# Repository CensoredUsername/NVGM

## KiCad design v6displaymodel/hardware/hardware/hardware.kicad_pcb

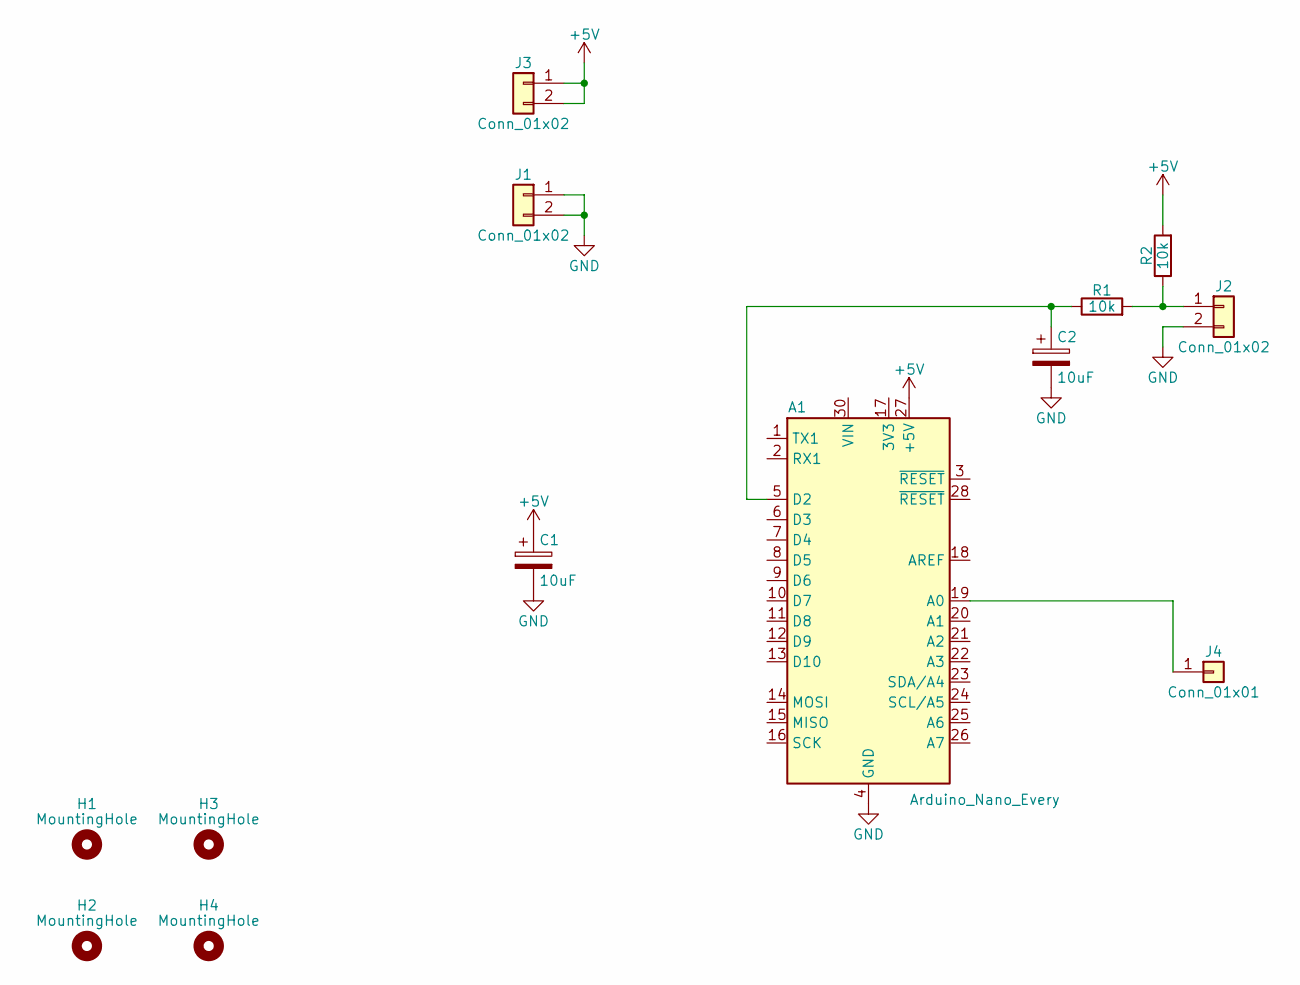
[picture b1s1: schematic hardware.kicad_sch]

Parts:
A1: Arduino_Nano_Every; Arduino_Nano
C1, C2: 10uF; CP_Radial_D5.0mm_P2.50mm
H1, H2, H3, H4: MountingHole; MountingHole_3.2mm_M3
J1, J2, J3: Conn_01x02; PinHeader_1x02_P2.54mm_Vertical
J4: Conn_01x01; PinHeader_1x01_P2.54mm_Vertical
R1, R2: 10k; R_Axial_DIN0204_L3.6mm_D1.6mm_P5.08mm_Horizontal

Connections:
+5V: A1.27 (+5V), C1.1, J3.1, J3.2, R2.2
GND: A1.4 (GND), A1.29 (GND), C1.2, C2.2, J1.1, J1.2, J2.2
unnamed: A1.5 (D2), C2.1, R1.1
unnamed: J2.1, R1.2, R2.1
unnamed: A1.19 (A0), J4.1

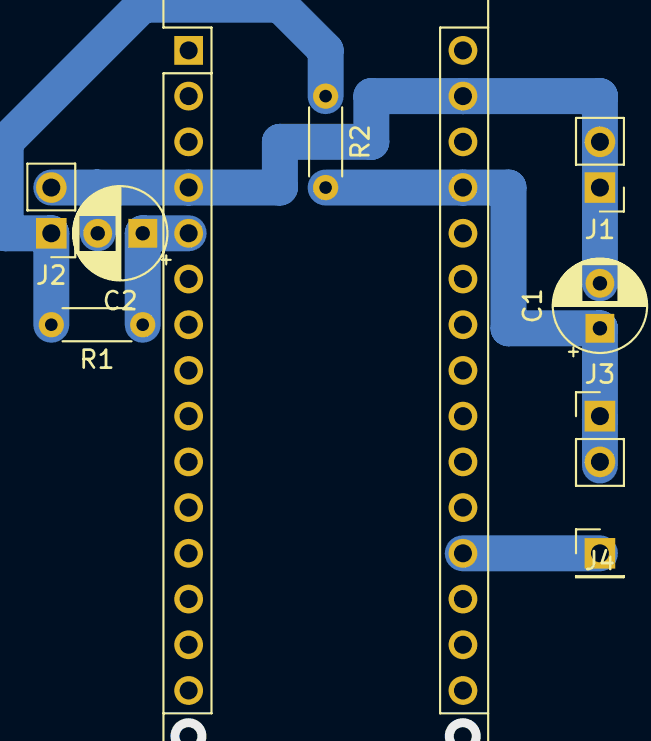
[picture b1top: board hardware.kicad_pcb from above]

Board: 2 copper layers, 13 parts (0 on the bottom side), 5 nets.

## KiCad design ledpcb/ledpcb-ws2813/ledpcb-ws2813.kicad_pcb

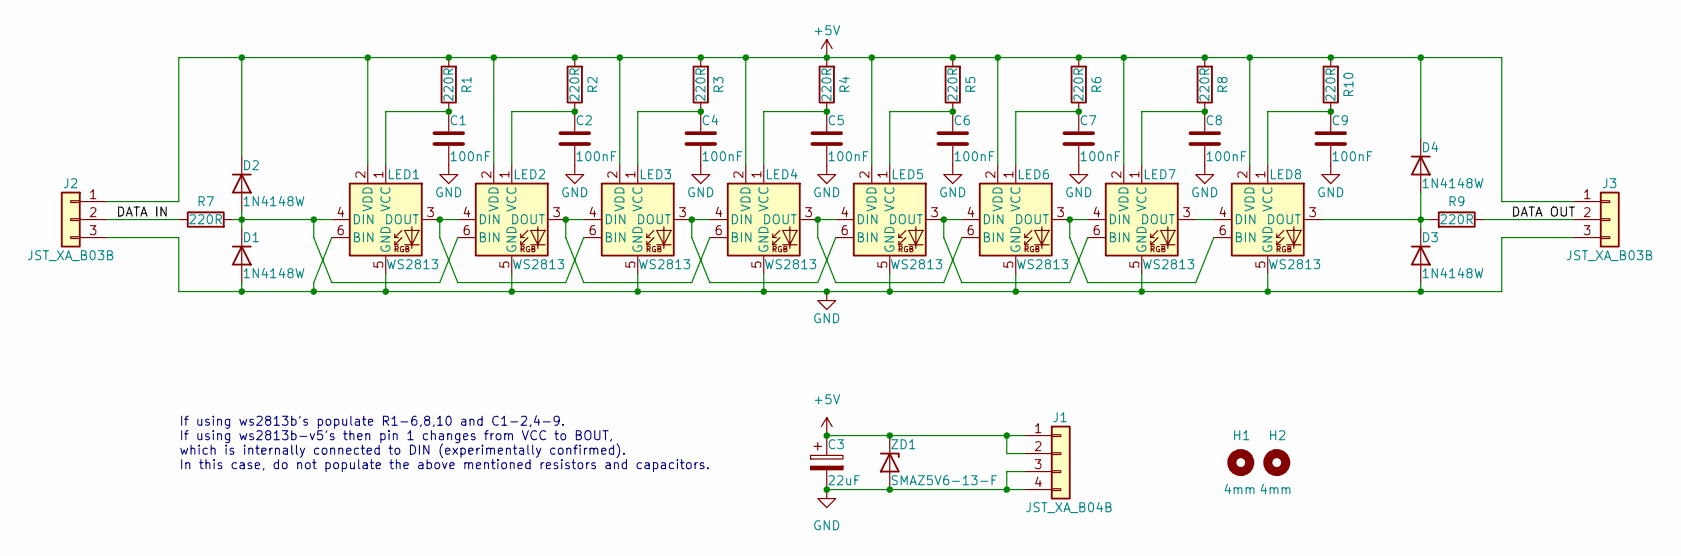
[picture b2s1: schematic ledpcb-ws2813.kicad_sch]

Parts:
C1, C2, C4, C5, C6, C7, C8, C9: 100nF; C_0603_1608Metric; LCSC C14663
C3: 22uF; C_Elec_6.3x5.4; LCSC C72505
D1, D2, D3, D4: 1N4148W; D_SOD-123; LCSC C81598
H1, H2: 4mm; MountingHole_3.2mm_M3
J1: JST_XA_B04B; JST_XA_B04B-XASK-1-A_1x04_P2.50mm_Vertical; LCSC C264994
J2, J3: JST_XA_B03B; JST_XA_B03B-XASK-1-A_1x03_P2.50mm_Vertical; LCSC C264992
LED1, LED2, LED3, LED4, LED5, LED6, LED7, LED8: WS2813; LED_WS2813_PLCC6_5.0x5.0mm_P1.6mm; LCSC C114592
R1, R2, R3, R4, R5, R6, R7, R8, R9, R10: 220R; R_0603_1608Metric; LCSC C22962
ZD1: SMAZ5V6-13-F; D_SMA; LCSC C5128847

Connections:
+5V: C3.1, D2.1 (K), D4.1 (K), J1.1, J1.2, J2.1, J3.1, LED1.2 (VDD), LED2.2 (VDD), LED3.2 (VDD), LED4.2 (VDD), LED5.2 (VDD), LED6.2 (VDD), LED7.2 (VDD), LED8.2 (VDD), R1.2, R2.2, R3.2, R4.2, R5.2, R6.2, R8.2, R10.2, ZD1.1 (K)
/DATA IN: J2.2, R7.1
/DATA OUT: J3.2, R9.1
GND: C1.2, C2.2, C3.2, C4.2, C5.2, C6.2, C7.2, C8.2, C9.2, D1.2 (A), D3.2 (A), J1.3, J1.4, J2.3, J3.3, LED1.5 (GND), LED1.6 (BIN), LED2.5 (GND), LED3.5 (GND), LED4.5 (GND), LED5.5 (GND), LED6.5 (GND), LED7.5 (GND), LED8.5 (GND), ZD1.2 (A)
unnamed: C1.1, LED1.1 (VCC), R1.1
unnamed: C2.1, LED2.1 (VCC), R2.1
unnamed: C4.1, LED3.1 (VCC), R3.1
unnamed: C5.1, LED4.1 (VCC), R4.1
unnamed: C6.1, LED5.1 (VCC), R5.1
unnamed: C7.1, LED6.1 (VCC), R6.1
unnamed: C8.1, LED7.1 (VCC), R8.1
unnamed: C9.1, LED8.1 (VCC), R10.1
unnamed: D1.1 (K), D2.2 (A), LED1.4 (DIN), LED2.6 (BIN), R7.2
unnamed: D3.1 (K), D4.2 (A), LED8.3 (DOUT), R9.2
unnamed: LED1.3 (DOUT), LED2.4 (DIN), LED3.6 (BIN)
unnamed: LED2.3 (DOUT), LED3.4 (DIN), LED4.6 (BIN)
unnamed: LED3.3 (DOUT), LED4.4 (DIN), LED5.6 (BIN)
unnamed: LED4.3 (DOUT), LED5.4 (DIN), LED6.6 (BIN)
unnamed: LED5.3 (DOUT), LED6.4 (DIN), LED7.6 (BIN)
unnamed: LED6.3 (DOUT), LED7.4 (DIN), LED8.6 (BIN)
unnamed: LED7.3 (DOUT), LED8.4 (DIN)

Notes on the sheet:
If using ws2813b's populate R1-6,8,10 and C1-2,4-9. If using ws2813b-v5's then pin 1 changes from VCC to BOUT, which is internally connected to DIN (experimentally confirmed). In this case, do not populate the above mentioned resistors and capacitors.

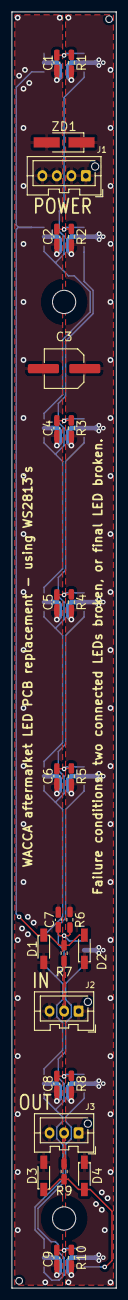
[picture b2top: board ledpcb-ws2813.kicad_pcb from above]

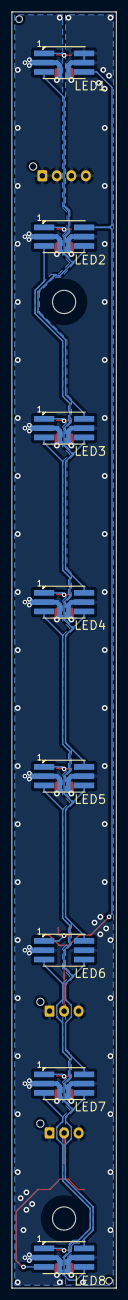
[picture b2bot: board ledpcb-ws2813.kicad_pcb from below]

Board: 2 copper layers, 18.0 x 220.0 mm, 37 parts (8 on the bottom side), 21 nets.

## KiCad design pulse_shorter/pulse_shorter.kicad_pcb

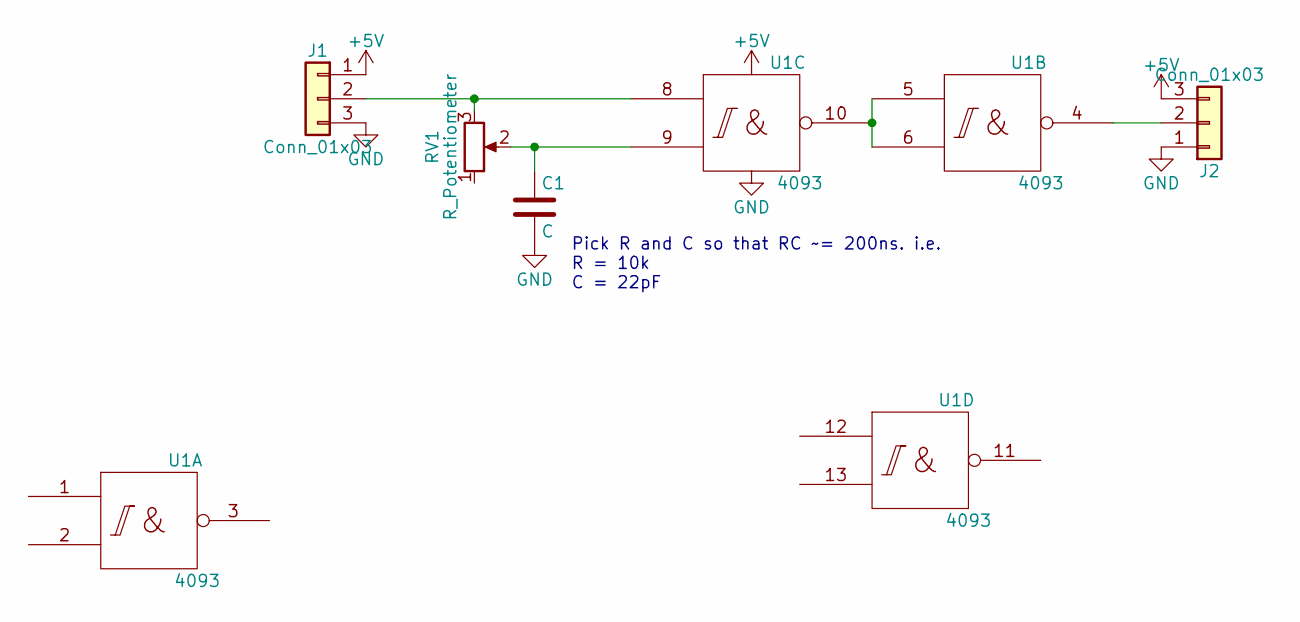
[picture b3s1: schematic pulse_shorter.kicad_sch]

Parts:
C1: C; C_Disc_D3.0mm_W1.6mm_P2.50mm
J1, J2: Conn_01x03; PinHeader_1x03_P2.54mm_Vertical
RV1: R_Potentiometer; Potentiometer_Piher_PT-6-V_Vertical
U1: 4093; DIP-14_W7.62mm

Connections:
+5V: J1.1, J2.3, U1.14 (Vdd)
GND: C1.2, J1.3, J2.1, U1.7 (Vss)
unnamed: C1.1, RV1.2, U1.9
unnamed: J1.2, RV1.3, U1.8
unnamed: J2.2, U1.4
unnamed: U1.5, U1.6, U1.10

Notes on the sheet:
Pick R and C so that RC ~= 200ns. i.e. R = 10k C = 22pF

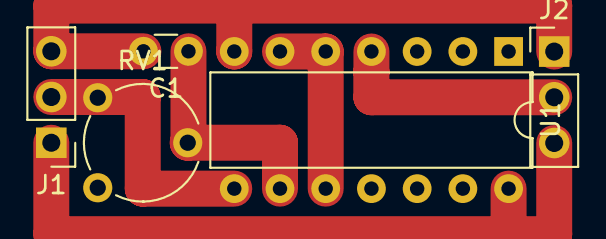
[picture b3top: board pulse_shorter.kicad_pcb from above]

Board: 2 copper layers, 5 parts (0 on the bottom side), 6 nets.

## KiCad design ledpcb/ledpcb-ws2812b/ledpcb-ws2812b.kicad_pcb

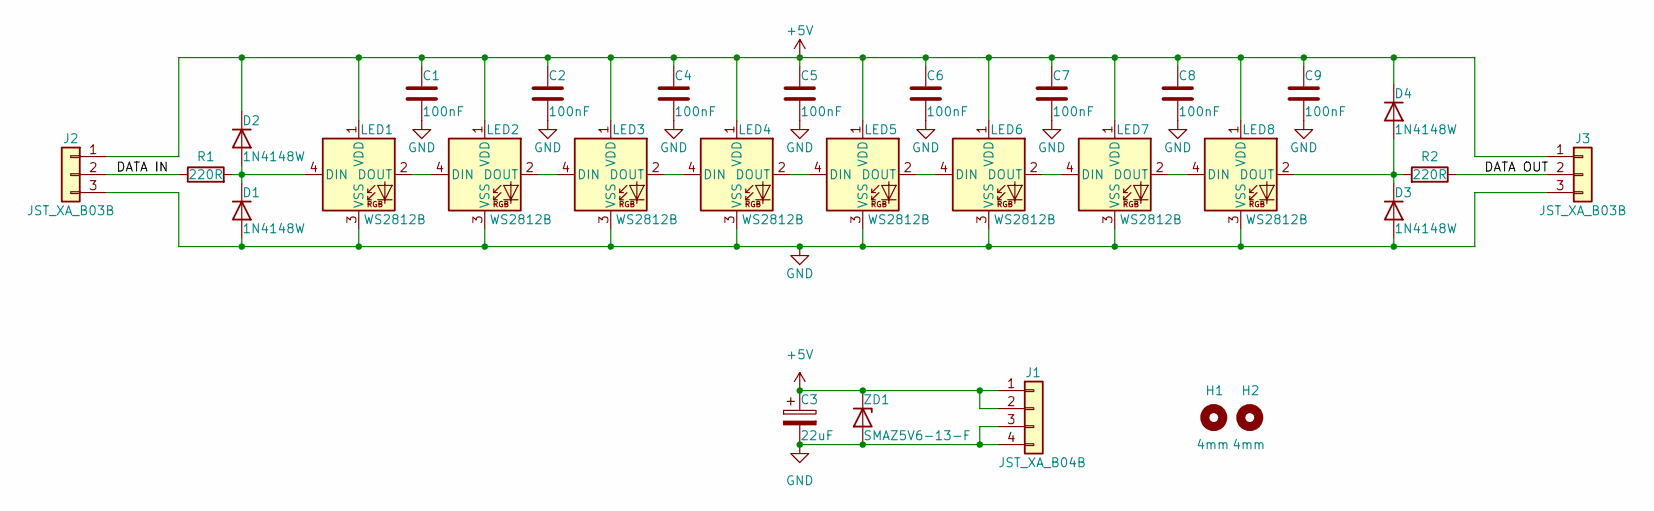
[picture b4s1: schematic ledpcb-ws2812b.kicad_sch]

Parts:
C1, C2, C4, C5, C6, C7, C8, C9: 100nF; C_0603_1608Metric; LCSC C14663
C3: 22uF; C_Elec_6.3x5.4; LCSC C72505
D1, D2, D3, D4: 1N4148W; D_SOD-123; LCSC C81598
H1, H2: 4mm; MountingHole_3.2mm_M3
J1: JST_XA_B04B; JST_XA_B04B-XASK-1-A_1x04_P2.50mm_Vertical; LCSC C264994
J2, J3: JST_XA_B03B; JST_XA_B03B-XASK-1-A_1x03_P2.50mm_Vertical; LCSC C264992
LED1, LED2, LED3, LED4, LED5, LED6, LED7, LED8: WS2812B; LED_WS2812B_PLCC4_5.0x5.0mm_P3.2mm; LCSC C2761795
R1, R2: 220R; R_0603_1608Metric; LCSC C22962
ZD1: SMAZ5V6-13-F; D_SMA; LCSC C110526

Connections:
+5V: C1.1, C2.1, C3.1, C4.1, C5.1, C6.1, C7.1, C8.1, C9.1, D2.1 (K), D4.1 (K), J1.1, J1.2, J2.1, J3.1, LED1.1 (VDD), LED2.1 (VDD), LED3.1 (VDD), LED4.1 (VDD), LED5.1 (VDD), LED6.1 (VDD), LED7.1 (VDD), LED8.1 (VDD), ZD1.1 (K)
/DATA IN: J2.2, R1.1
/DATA OUT: J3.2, R2.1
GND: C1.2, C2.2, C3.2, C4.2, C5.2, C6.2, C7.2, C8.2, C9.2, D1.2 (A), D3.2 (A), J1.3, J1.4, J2.3, J3.3, LED1.3 (VSS), LED2.3 (VSS), LED3.3 (VSS), LED4.3 (VSS), LED5.3 (VSS), LED6.3 (VSS), LED7.3 (VSS), LED8.3 (VSS), ZD1.2 (A)
unnamed: D1.1 (K), D2.2 (A), LED1.4 (DIN), R1.2
unnamed: D3.1 (K), D4.2 (A), LED8.2 (DOUT), R2.2
unnamed: LED1.2 (DOUT), LED2.4 (DIN)
unnamed: LED2.2 (DOUT), LED3.4 (DIN)
unnamed: LED3.2 (DOUT), LED4.4 (DIN)
unnamed: LED4.2 (DOUT), LED5.4 (DIN)
unnamed: LED5.2 (DOUT), LED6.4 (DIN)
unnamed: LED6.2 (DOUT), LED7.4 (DIN)
unnamed: LED7.2 (DOUT), LED8.4 (DIN)

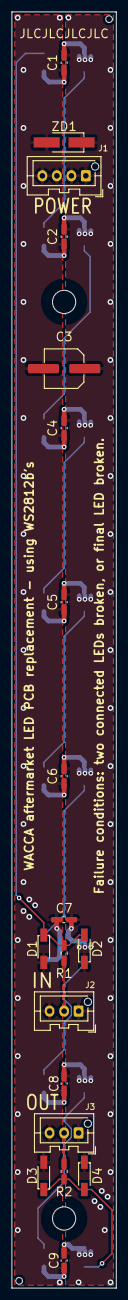
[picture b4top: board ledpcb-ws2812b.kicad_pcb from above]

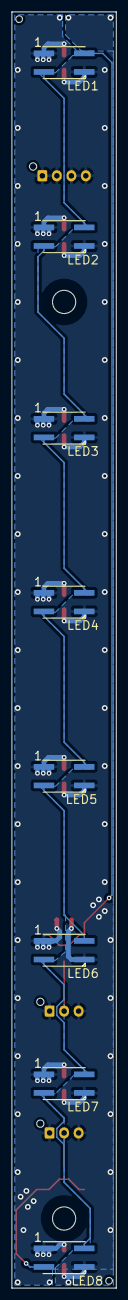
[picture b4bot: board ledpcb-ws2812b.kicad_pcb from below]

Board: 2 copper layers, 18.0 x 220.0 mm, 29 parts (8 on the bottom side), 13 nets.

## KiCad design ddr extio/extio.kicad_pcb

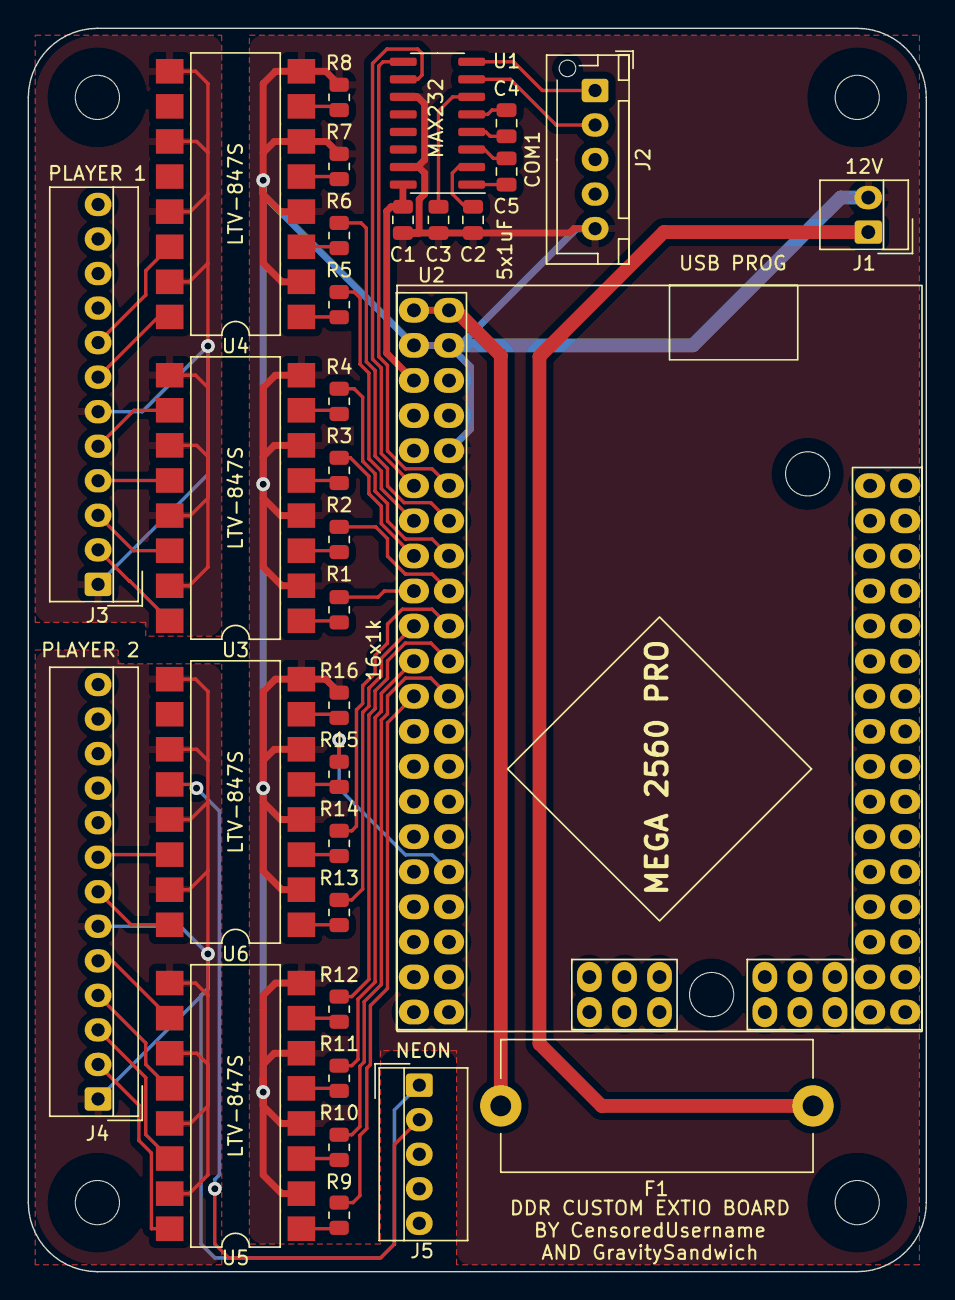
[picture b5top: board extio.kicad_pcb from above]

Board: 2 copper layers, 65.0 x 90.0 mm, 37 parts (0 on the bottom side), 58 nets.

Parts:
C1, C2, C3, C4, C5: 1uF; C_0805_2012Metric
F1: ?A; Fuseholder_Cylinder-5x20mm_Stelvio-Kontek_PTF78_Horizontal_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
H1, H2, H3, H4: M3; MountingHole_3.2mm_M3
J1: JST_NH_B02; JST_NH_B2P-SHF-1AA_1x02_P2.50mm_Vertical
J2: JST_XH_B05; JST_XH_B5B-XH-AM_1x05_P2.50mm_Vertical
J3: JST_NH_B12; JST_NH_B12P-SHF-1AA_1x12_P2.50mm_Vertical
J4: JST_NH_B13; JST_NH_B13P-SHF-1AA_1x13_P2.50mm_Vertical
J5: JST_NH_B05; JST_NH_B5P-SHF-1AA_1x05_P2.50mm_Vertical
R1, R2, R3, R4, R5, R6, R7, R8, R9, R10, R11, R12, R13, R14, R15, R16: 1k; R_0805_2012Metric
U1: MAX232; SOIC-16_3.9x9.9mm_P1.27mm
U2: Arduino_mega_2560_pro
U3, U4, U5, U6: LTV-847S; SMDIP-16_W9.53mm

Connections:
+5V: C1.1, U1.16 (VCC), U2.6 (5V)
+12V: F1.1, U2.1 (VIN), U2.2 (VIN)
/isolation1/Input A: R1.2, U2.18 (D7)
/isolation1/Input B: R2.2, U2.17 (D6)
/isolation1/Input C: R3.2, U2.16 (D5)
/isolation1/Input D: R4.2, U2.15 (D4)
/isolation1/Output A: J3.2, U3.16
/isolation1/Output B: J3.3, U3.14
/isolation1/Output C: J3.4, U3.12
/isolation1/Output D: J3.5, U3.10
/isolation2/Input A: R13.2, U2.20 (D9)
/isolation2/Input B: R14.2, U2.19 (D8)
/isolation2/Input C: R15.2, U2.33 (D22)
/isolation2/Output A: J4.7, U6.16
/isolation2/Output B: J4.8, U6.14
/isolation2/Output C: J5.2, U6.12
/isolation2/Output GND: J4.1, J4.6, J5.1, U5.9, U5.11, U5.13, U5.15, U6.9, U6.11, U6.13, U6.15
/isolation3/Input A: R9.2, U2.24 (D13)
/isolation3/Input B: R10.2, U2.23 (D12)
/isolation3/Input C: R11.2, U2.22 (D11)
/isolation3/Input D: R12.2, U2.21 (D10)
/isolation3/Output A: J4.2, U5.16
/isolation3/Output B: J4.3, U5.14
/isolation3/Output C: J4.4, U5.12
/isolation3/Output D: J4.5, U5.10
/isolation/Input A: R5.2, U2.14 (D3)
/isolation/Input B: R6.2, U2.13 (D2)
/isolation/Output A: J3.7, U4.16
/isolation/Output B: J3.8, U4.14
/isolation/Output GND: J3.1, J3.6, U3.9, U3.11, U3.13, U3.15, U4.9, U4.11, U4.13, U4.15
GND: C1.2, C2.2, C3.2, J1.2, J2.5, R7.2, R8.2, R16.2, U1.11 (T1IN), U1.15 (GND), U2.3 (GND), U2.4 (GND), U2.9 (AREF), U3.2, U3.4, U3.6, U3.8, U4.2, U4.4, U4.6, U4.8, U5.2, U5.4, U5.6, U5.8, U6.2, U6.4, U6.6, U6.8
unnamed: C2.1, U1.2 (VS+)
unnamed: C3.1, U1.6 (VS-)
unnamed: C4.1, U1.4 (C2+)
unnamed: C4.2, U1.5 (C2-)
unnamed: C5.1, U1.1 (C1+)
unnamed: C5.2, U1.3 (C1-)
unnamed: F1.2, J1.1
unnamed: J2.1, U1.8 (R2IN)
unnamed: J2.2, U1.7 (T2OUT)
unnamed: R1.1, U3.1
unnamed: R2.1, U3.3
unnamed: R3.1, U3.5
unnamed: R4.1, U3.7
unnamed: R5.1, U4.1
unnamed: R6.1, U4.3
unnamed: R7.1, U4.5
unnamed: R8.1, U4.7
unnamed: R9.1, U5.1
unnamed: R10.1, U5.3
unnamed: R11.1, U5.5
unnamed: R12.1, U5.7
unnamed: R13.1, U6.1
unnamed: R14.1, U6.3
unnamed: R15.1, U6.5
unnamed: R16.1, U6.7
unnamed: U1.9 (R2OUT), U2.11 (RX)
unnamed: U1.10 (T2IN), U2.12 (TX)

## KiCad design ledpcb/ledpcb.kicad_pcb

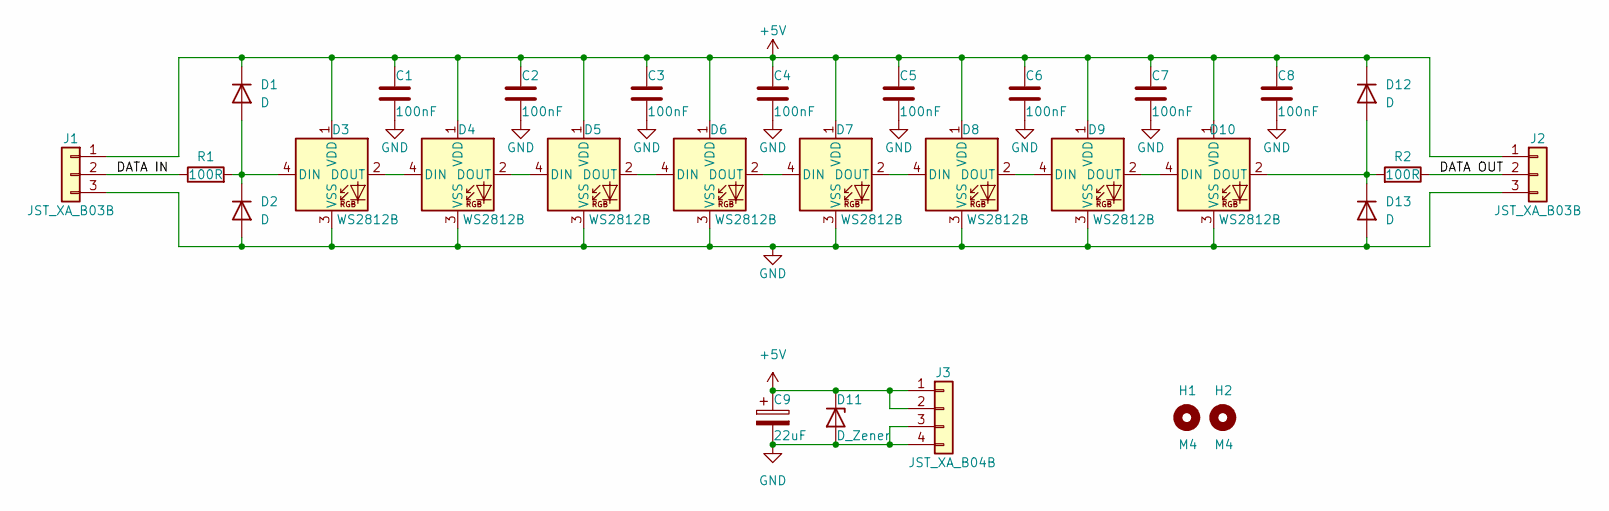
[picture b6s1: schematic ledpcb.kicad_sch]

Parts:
C1, C2, C3, C4, C5, C6, C7, C8: 100nF; C_0603_1608Metric
C9: 22uF; C_Elec_6.3x5.4
D1, D2, D12, D13: D; D_SOD-123
D3, D4, D5, D6, D7, D8, D9, D10: WS2812B; LED_WS2812B_PLCC4_5.0x5.0mm_P3.2mm
D11: D_Zener; D_SMA
H1, H2: M4; MountingHole_4.3mm_M4
J1, J2: JST_XA_B03B; JST_XA_B03B-XASK-1-A_1x03_P2.50mm_Vertical
J3: JST_XA_B04B; JST_XA_B04B-XASK-1-A_1x04_P2.50mm_Vertical
R1, R2: 100R; R_0603_1608Metric

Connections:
+5V: C1.1, C2.1, C3.1, C4.1, C5.1, C6.1, C7.1, C8.1, C9.1, D1.1 (K), D3.1 (VDD), D4.1 (VDD), D5.1 (VDD), D6.1 (VDD), D7.1 (VDD), D8.1 (VDD), D9.1 (VDD), D10.1 (VDD), D11.1 (K), D12.1 (K), J1.1, J2.1, J3.1, J3.2
/DATA IN: J1.2, R1.1
/DATA OUT: J2.2, R2.1
GND: C1.2, C2.2, C3.2, C4.2, C5.2, C6.2, C7.2, C8.2, C9.2, D2.2 (A), D3.3 (VSS), D4.3 (VSS), D5.3 (VSS), D6.3 (VSS), D7.3 (VSS), D8.3 (VSS), D9.3 (VSS), D10.3 (VSS), D11.2 (A), D13.2 (A), J1.3, J2.3, J3.3, J3.4
unnamed: D3.2 (DOUT), D4.4 (DIN)
unnamed: D1.2 (A), D2.1 (K), D3.4 (DIN), R1.2
unnamed: D4.2 (DOUT), D5.4 (DIN)
unnamed: D5.2 (DOUT), D6.4 (DIN)
unnamed: D6.2 (DOUT), D7.4 (DIN)
unnamed: D7.2 (DOUT), D8.4 (DIN)
unnamed: D8.2 (DOUT), D9.4 (DIN)
unnamed: D10.2 (DOUT), D12.2 (A), D13.1 (K), R2.2
unnamed: D9.2 (DOUT), D10.4 (DIN)

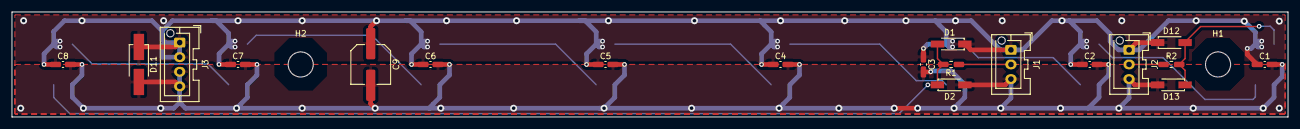
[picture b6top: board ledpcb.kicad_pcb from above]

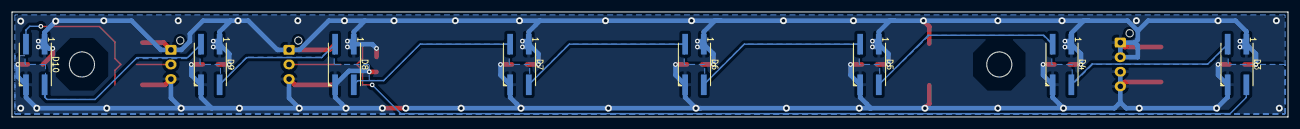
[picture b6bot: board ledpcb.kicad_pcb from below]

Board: 2 copper layers, 218.8 x 18.0 mm, 29 parts (8 on the bottom side), 13 nets.

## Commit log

2022-05-22 ledstripesplitter working
2022-05-23 Add flashing tool schematic, reorganize arduino files so the ide doesn't get confused, and improve ledstripesplitter so it even retimes the high pulses if the input is out of whack.
2022-05-26 Desktop work
2022-06-05 Add basic promp dumping tools and dump the prom.
2022-06-07 Write disassembler and start reversing code.
2022-06-07 also save notes.
2022-06-08 More decompiled code
2022-06-09 More work.
2022-06-14 finish decompiling
2022-06-14 Name final function
2022-06-15 Some updates
2022-06-29 Reorganize all the things, add some extra sanity checking and bring everything up to date with reality. Additionally add a README describing everything in coincounter.
2022-07-24 Final tweaks to ledsplitter pin mapping and segment length, now confirmed working
2022-08-11 Add ledstripesplitter README.
2022-08-19 led pcb work.
2022-08-23 Work on extio pcb
2022-08-31 Ledpcb designs, ready for ordering.
2022-09-08 Changes for ordering with JLCPCB.
2022-12-08 Ledstripetester/splitter: updates to both, add support for ledstripesplitter to render a full framebuffer to a led array before switching to splitting mode for led testing.
2022-12-08 Add ddr extio gitignore.
2022-12-08 make lib paths relative
2022-12-08 Add jlcpcb pcb mounting hole component.
2023-02-09 Ledmatrix board work.
2023-02-10 Temp commit to move computers.
2023-02-12 Finish ledmatrix pcb reverse engineering.
2023-04-02 switch to desktop
2023-04-06 Work on led matrix display.
2023-07-07 add ws2813 pulse shortener.
2023-07-07 Add comment about RC values
2024-03-28 replace C110526 by C2844869
2024-03-28 Just use white light for the tester.
2024-03-28 move zd1 from 1SMA4734 to 1SMA4734A.
2024-06-19 add v6 display model to the repo, and some software / hardware design files.
2024-06-26 Add v6 display model hardware files.
2025-08-10 Add hardware and Jeroen's software for the led display.
2025-08-10 Fix LED display geometry logic
2025-08-10 Fix Jeroen code.
2025-08-10 Fix Maurits code.
2025-08-10 Speed up Maurits code.
2025-08-10 Add some amount of documentation.
